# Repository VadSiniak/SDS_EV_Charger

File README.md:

# SDS_EV_Charger
Project helps to make your own low cost EV Charger

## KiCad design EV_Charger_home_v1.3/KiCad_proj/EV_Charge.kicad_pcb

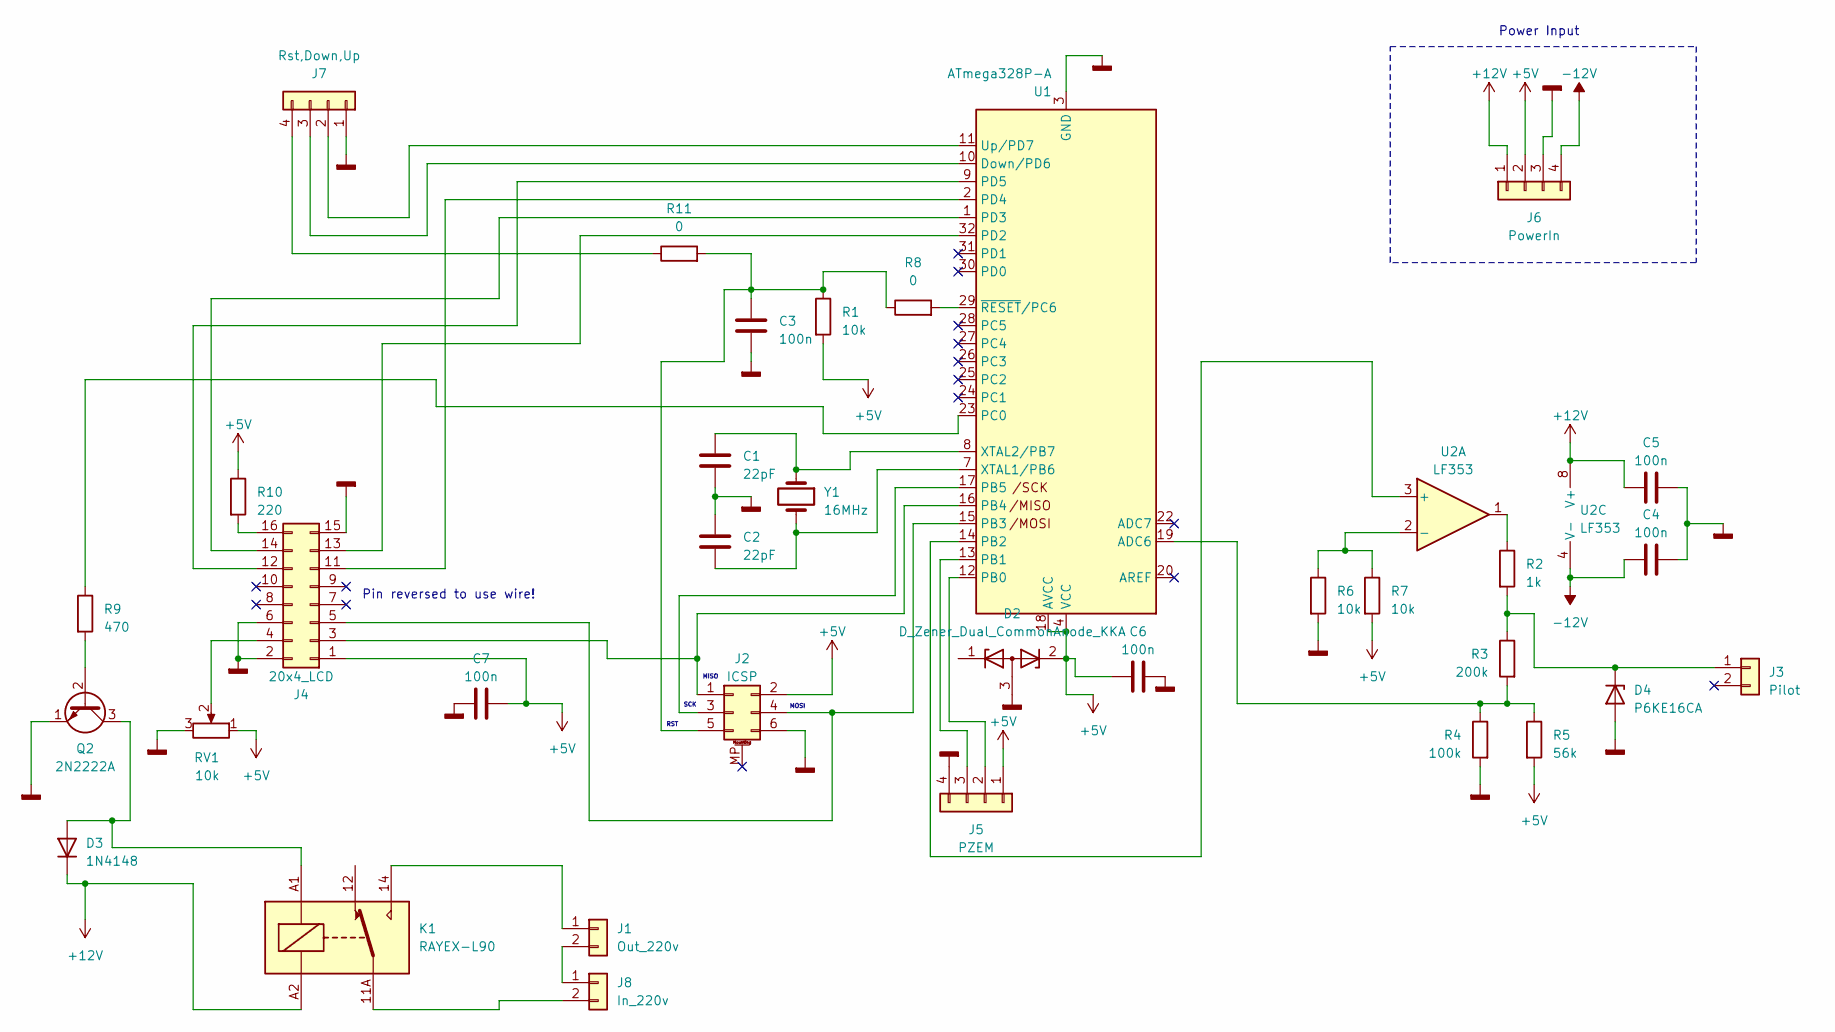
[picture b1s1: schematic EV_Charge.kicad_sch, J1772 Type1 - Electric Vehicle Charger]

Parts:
C1, C2: 22pF; C_1206_3216Metric_Pad1.33x1.80mm_HandSolder
C3, C4, C5, C6, C7: 100n; C_1206_3216Metric_Pad1.33x1.80mm_HandSolder
D2: D_Zener_Dual_CommonAnode_KKA; TSOT-23
D3: 1N4148; D_DO-15_P5.08mm_Vertical_KathodeUp
D4: P6KE16CA; D_SMB_Handsoldering
J1: Out_220v; Connector_DG950-9.5-Housing
J2: ICSP; PinHeader_2x03_P2.54mm_Vertical
J3: Pilot; PhoenixContact_MCV_1,5_2-G-3.5_1x02_P3.50mm_Vertical
J4: 20x4_LCD; IDC-Header_2x08_P2.54mm_Vertical
J5: PZEM; PhoenixContact_MCV_1,5_4-G-3.5_1x04_P3.50mm_Vertical
J6: PowerIn; PhoenixContact_MCV_1,5_4-G-3.5_1x04_P3.50mm_Vertical
J7: Rst,Down,Up; PhoenixContact_MCV_1,5_4-G-3.5_1x04_P3.50mm_Vertical
J8: In_220v; Connector_DG950-9.5-Housing
K1: RAYEX-L90; Relay_SPDT_RAYEX-L90
Q2: 2N2222A; TO-92L_Wide
R1, R6, R7: 10k; R_2010_5025Metric_Pad1.40x2.65mm_HandSolder
R2: 1k; R_2010_5025Metric_Pad1.40x2.65mm_HandSolder
R3: 200k; R_2010_5025Metric_Pad1.40x2.65mm_HandSolder
R4: 100k; R_2010_5025Metric_Pad1.40x2.65mm_HandSolder
R5: 56k; R_2512_6332Metric_Pad1.40x3.35mm_HandSolder
R8, R11: 0; R_2010_5025Metric_Pad1.40x2.65mm_HandSolder
R9: 470; R_2010_5025Metric_Pad1.40x2.65mm_HandSolder
R10: 220; R_2010_5025Metric_Pad1.40x2.65mm_HandSolder
RV1: 10k; Potentiometer_Runtron_RM-065_Vertical
U1: ATmega328P-A; TQFP-32_7x7mm_P0.8mm
U2: LF353; SO-8_3.9x4.9mm_P1.27mm
Y1: 16MHz; Crystal_SMD_HC49-SD

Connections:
+5V: C6.1, C7.1, D2.2 (K), J2.2, J4.1, J5.1, J6.2, R1.2, R5.2, R7.2, R10.1, RV1.1, U1.4 (VCC), U1.6 (VCC), U1.18 (AVCC)
+12V: C5.1, D3.1 (K), J6.1, K1.A2, U2.8 (V+)
-12V: C4.1, J6.4, U2.4 (V-)
GNDD: C1.2, C2.1, C3.2, C4.2, C5.2, C6.2, C7.2, D2.3 (A), D4.2 (A), J2.6, J4.2, J4.6, J4.15, J5.4, J6.3, J7.1, Q2.1 (E), R4.2, R6.2, RV1.3, U1.3 (GND), U1.5 (GND), U1.21 (GND)
unnamed: D3.2 (A), K1.A1, Q2.3 (C)
unnamed: D4.1 (K), J3.1, R2.2, R3.1
unnamed: J1.1, K1.14
unnamed: J1.2, J8.1
unnamed: J2.1, J4.3, U1.16 (PB4)
unnamed: J2.3, U1.17 (PB5)
unnamed: J2.4, J4.5, U1.15 (PB3)
unnamed: C3.1, J2.5, R1.1, R8.1, R11.2
unnamed: J4.4, RV1.2
unnamed: J4.11, U1.2 (PD4)
unnamed: J4.12, U1.9 (PD5)
unnamed: J4.13, U1.32 (PD2)
unnamed: J4.14, U1.1 (PD3)
unnamed: J4.16, R10.2
unnamed: J5.2, U1.12 (PB0)
unnamed: J5.3, U1.13 (PB1)
unnamed: J7.2, U1.11 (Up/PD7)
unnamed: J7.3, U1.10 (Down/PD6)
unnamed: J7.4, R11.1
unnamed: J8.2, K1.11A, K1.11B
unnamed: Q2.2 (B), R9.2
unnamed: R2.1, U2.1
unnamed: R3.2, R4.1, R5.1, U1.19 (ADC6)
unnamed: U1.14 (PB2), U2.3 (+)
unnamed: R9.1, U1.23 (PC0)
unnamed: C2.2, U1.7 (XTAL1/PB6), Y1.2
unnamed: C1.1, U1.8 (XTAL2/PB7), Y1.1
unnamed: R8.2, U1.29 (~RESET/PC6)
unnamed: R6.1, R7.1, U2.2 (-)

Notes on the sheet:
SCK
Pin reversed to use wire!
Power Input
MOSI
MISO
RST

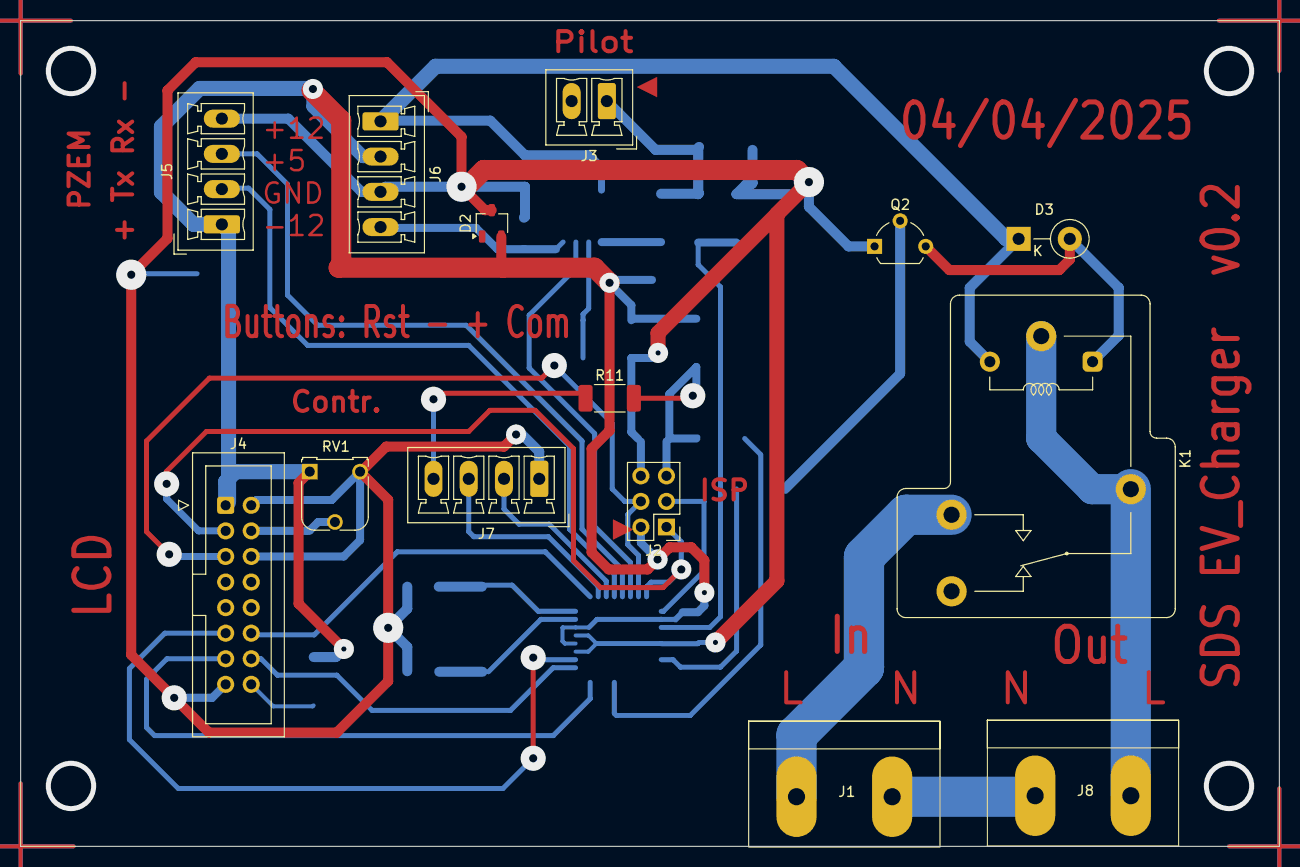
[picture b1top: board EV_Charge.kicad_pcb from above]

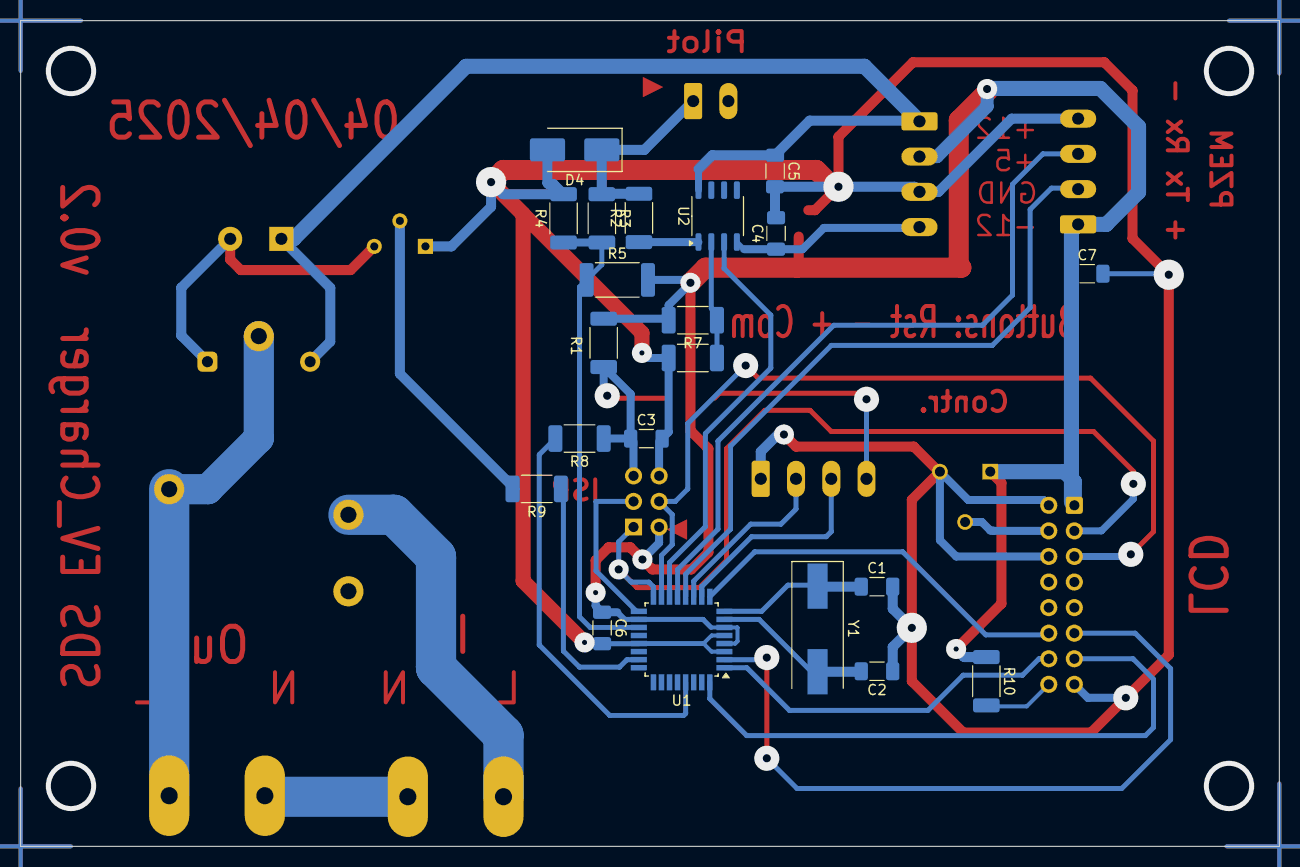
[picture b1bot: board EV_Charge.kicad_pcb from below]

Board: 2 copper layers, 125.0 x 82.0 mm, 35 parts (21 on the bottom side), 33 nets.

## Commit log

2025-04-10 Create EV_Charger_home_v1.3.ino
    Added Arduino project file
2025-04-10 Added J1772 and LCD signaling circuit images
2025-04-10 Added KiCad8 project
2025-06-30 Improved button function
